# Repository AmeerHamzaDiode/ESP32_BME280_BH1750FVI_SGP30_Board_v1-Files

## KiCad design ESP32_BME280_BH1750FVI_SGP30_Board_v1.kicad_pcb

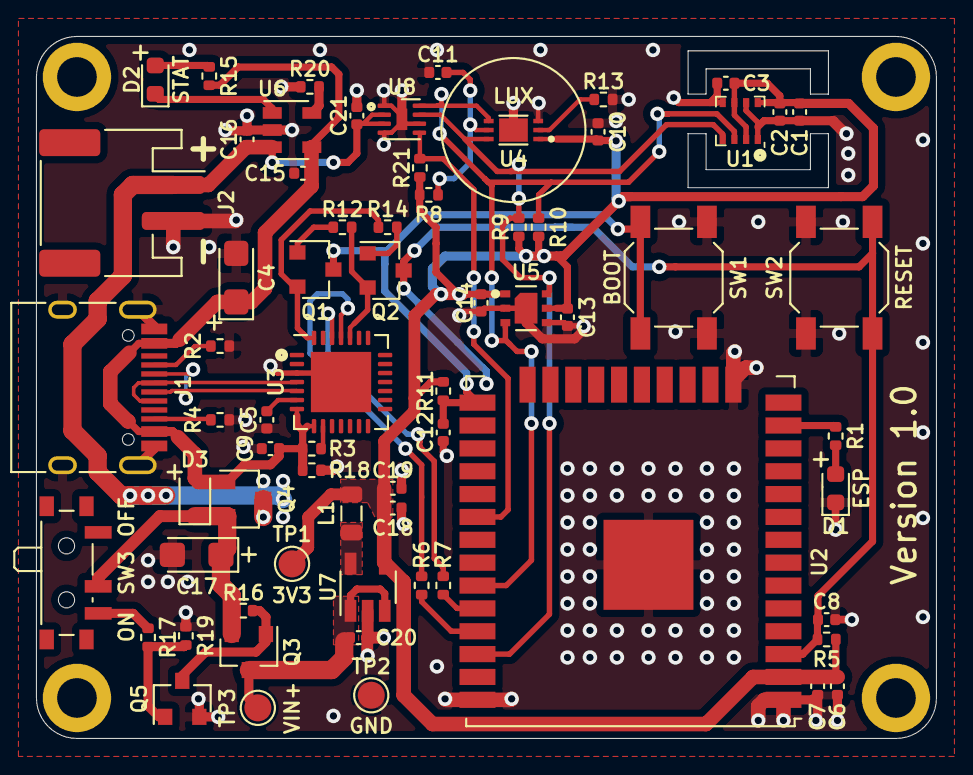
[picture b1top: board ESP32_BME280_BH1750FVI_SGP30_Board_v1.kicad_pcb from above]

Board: 2 copper layers, 50.0 x 39.0 mm, 71 parts (0 on the bottom side), 36 nets.

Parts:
C1, C6, C15, C16, C18: 10uF; C_0402_1005Metric
C2, C3, C5, C7, C9, C10, C14, C19, C21: 0.1uF; C_0402_1005Metric
C4, C17: 10uF; CP_EIA-3216-18_Kemet-A
C8, C11, C12, C13: 1uF; C_0402_1005Metric
C20: 4.7uF; C_0402_1005Metric
D1: ESP; LED_0603_1608Metric
D2: STAT; LED_0603_1608Metric
D3: 1N5819WS; D_SOD-323
H1, H2, H3, H4: M2; MountingHole_2.2mm_M2_DIN965_Pad
J1: TYPE-C-31-M-12; USB_C_Receptacle_HRO_TYPE-C-31-M-12
J2: S2B-PH; JST_PH_S2B-PH-SM4-TB_1x02-1MP_P2.00mm_Horizontal
L1: 2.2uH; L_0805_2012Metric
Q1, Q2: SS8050; SOT-23
Q3, Q4: SI2301CDS-T1-GE3; SOT-23
Q5: 2N7002; SOT-23
R1, R17: 470R; R_0402_1005Metric
R2, R4: 5.1K; R_0402_1005Metric
R3, R5, R9, R10, R11, R12, R14, R16, R19, R21: 10K; R_0402_1005Metric
R6, R7, R8, R13, R15: 1K; R_0402_1005Metric
R18: 100K; R_0402_1005Metric
R20: 2K; R_0402_1005Metric
SW1: BOOT; SW_SPST_SKQG_WithoutStem
SW2: RESET; SW_SPST_SKQG_WithoutStem
SW3: K3-1296S-E1; Slide_switch_K3-1296S-E1
TP1: 3V3; TestPoint_Pad_D1.5mm
TP2: GND; TestPoint_Pad_D1.5mm
TP3: VIN+; TestPoint_Pad_D1.5mm
U1: BME280; Bosch_LGA-8_2.5x2.5mm_P0.65mm_ClockwisePinNumbering
U2: ESP32-WROOM-32UE-N8; ESP32-WROOM-32U
U3: CP2102-GMR; QFN-28-1EP_5x5mm_P0.5mm_EP3.35x3.35mm
U4: BH1750FVI-TR
U5: SGP30-2.5K; SGP40-D-R4
U6: MCP73831T-2ACI/OT; SOT-23-5
U7: LM3671MFX-3.3/NOPB; TSOT-23-5
U8: MAX17048G+T10; DFN-8-1EP_2x2mm_P0.5mm_EP0.6x1.2mm

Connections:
+3V3: C1.1, C2.1, C3.1, C6.1, C7.1, C10.1, C13.1, C14.1, C18.1, C19.1, L1.2, R5.2, R8.1, R9.1, R10.1, R11.2, R21.1, TP1.1, U1.2, U1.6, U1.8, U2.2, U4.1, U5.1, U5.5, U7.4
+BATT: C16.1, C21.1, J2.1, Q4.3, U6.3, U8.2, U8.3
/PWR+: C17.1, D3.1, Q3.2, Q4.2, R16.1, SW3.2
/VIN+: C20.1, Q3.3, TP3.1, U7.1, U7.3
BOOT: C12.1, Q1.3, R11.1, SW1.2, U2.25
D+: J1.A6, J1.B6, U3.4
D-: J1.A7, J1.B7, U3.5
DTR: Q1.2, R14.1, U3.28
GND: C1.2, C2.2, C3.2, C4.2, C5.2, C6.2, C7.2, C8.2, C9.2, C10.2, C11.2, C12.2, C13.2, C14.2, C15.2, C16.2, C17.2, C18.2, C19.2, C20.2, C21.2, D1.1, J1.A1, J1.A12, J1.B1, J1.B12, J1.S1, J2.2, Q5.2, R2.1, R4.1, R13.2, R18.2, R19.2, R20.2, SW1.1, SW2.1, TP2.1, U1.1, U1.5, U1.7, U2.1, U2.15, U2.38, U2.39, U3.3, U3.29, U4.3, U4.7, U5.2, U5.4, U5.7, U6.2, U7.2, U8.1, U8.4, U8.6, U8.9
IO14: R1.1, U2.13
IO18: R21.2, U2.30, U8.5
unnamed: C5.1, U3.6
unnamed: C11.1, R8.2, U4.5
unnamed: D1.2, R1.2
unnamed: D2.1, U6.1
unnamed: D2.2, R15.2
unnamed: J1.A5, R2.2
unnamed: J1.B5, R4.2
unnamed: L1.1, U7.5
unnamed: Q1.1, R12.2
unnamed: Q2.1, R14.2
unnamed: Q3.1, Q5.3, R16.2
unnamed: Q5.1, R17.1, R19.1
unnamed: R3.2, U3.9
unnamed: R6.1, U2.35
unnamed: R7.2, U2.34
unnamed: R13.1, U4.2
unnamed: R17.2, SW3.3
unnamed: R20.1, U6.5
RESET: C8.1, Q2.3, R5.1, SW2.2, U2.3
RTS: Q2.2, R12.1, U3.24
RXD: R6.2, U3.25
SCL: R9.2, U1.4, U2.36, U4.6, U5.6, U8.7
SDA: R10.2, U1.3, U2.33, U4.4, U5.3, U8.8
TXD: R7.1, U3.26
VBUS: C4.1, C9.1, C15.1, D3.2, J1.A4, J1.A9, J1.B4, J1.B9, Q4.1, R3.1, R15.1, R18.1, U3.7, U3.8, U6.4

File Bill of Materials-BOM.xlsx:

Designator | Comment | Quantity | Footprint | Manufacturer Name | Manufacturer Part # | JLCPCB Part #
C18,C16,C15,C6,C1 | 10uF | 5 | C_0402_1005Metric | Samsung Electro-Mechanics | CL05A106MQ5NUNC | C15525
C21,C19,C14,C10,C9,C7,C5,C3,C2 | 0.1uF | 9 | C_0402_1005Metric | Samsung Electro-Mechanics | CL05B104KO5NNNC | C1525
C17,C4 | 10uF | 2 | CP_EIA-3216-18_Kemet-A | KYOCERA AVX | TAJA106K016RNJ | C7171
C13,C12,C11,C8 | 1uF | 4 | C_0402_1005Metric | Samsung Electro-Mechanics | CL05A105KA5NQNC | C52923
C20 | 4.7uF | 1 | C_0402_1005Metric | Samsung Electro-Mechanics | CL05A475MP5NRNC | C23733
D1 | ESP | 1 | LED_0603_1608Metric | Hubei KENTO Elec | KT-0603W | C2290
D2 | STAT | 1 | LED_0603_1608Metric | Hubei KENTO Elec | KT-0603R | C2286
D3 | 1N5819WS | 1 | D_SOD-323 | Guangdong Hottech | 1N5819WS | C191023
J1 | TYPE-C-31-M-12 | 1 | USB_C_Receptacle_HRO_TYPE-C-31-M-12 | Korean Hroparts Elec | TYPE-C-31-M-12 | C165948
J2 | S2B-PH | 1 | JST_PH_S2B-PH-SM4-TB_1x02-1MP_P2.00mm_Horizontal | JST | S2B-PH-SM4-TB(LF)(SN) | C295747
L1 | 2.2uH | 1 | L_0805_2012Metric | FH (Guangdong Fenghua Advanced Tech) | CMH201209B2R2MTD | C394957
Q2,Q1 | SS8050 | 2 | SOT-23 | Jiangsu Changjing Electronics Technology Co., Ltd. | SS8050(RANGE:200-350) | C2150
Q4,Q3 | SI2301CDS-T1-GE3 | 2 | SOT-23 | Vishay Intertech | SI2301CDS-T1-GE3 | C10487
Q5 | 2N7002 | 1 | SOT-23 | Jiangsu Changjing Electronics Technology Co., Ltd. | 2N7002 | C8545
R17,R1 | 470R | 2 | R_0402_1005Metric | UNI-ROYAL(Uniroyal Elec) | 0402WGF4700TCE | C25117
R4,R2 | 5.1K | 2 | R_0402_1005Metric | UNI-ROYAL(Uniroyal Elec) | 0402WGF5101TCE | C25905
R21,R19,R16,R14,R12,R11,R10,R9,R5,R3 | 10K | 10 | R_0402_1005Metric | UNI-ROYAL(Uniroyal Elec) | 0402WGF1002TCE | C25744
R15,R13,R8,R7,R6 | 1K | 5 | R_0402_1005Metric | UNI-ROYAL(Uniroyal Elec) | 0402WGF1001TCE | C11702
R18 | 100K | 1 | R_0402_1005Metric | UNI-ROYAL(Uniroyal Elec) | 0402WGF1003TCE | C25741
R20 | 2K | 1 | R_0402_1005Metric | UNI-ROYAL(Uniroyal Elec) | 0402WGF2001TCE | C4109
SW1 | BOOT | 1 | SW_SPST_SKQG_WithoutStem | XKB Connection | TS-1187A-B-A-B | C318884
SW2 | RESET | 1 | SW_SPST_SKQG_WithoutStem | XKB Connection | TS-1187A-B-A-B | C318884
SW3 | K3-1296S-E1 | 1 | Slide_switch_K3-1296S-E1 | Korean Hroparts Elec | K3-1296S-E1 | C128955
U1 | BME280 | 1 | Bosch_LGA-8_2.5x2.5mm_P0.65mm_ClockwisePinNumbering | Bosch Sensortec | BME280 | C92489
U2 | ESP32-WROOM-32UE-N8 | 1 | ESP32-WROOM-32U | Espressif Systems | ESP32-WROOM-32UE-N8 | C701345
U3 | CP2102-GMR | 1 | QFN-28-1EP_5x5mm_P0.5mm_EP3.35x3.35mm | SKYWORKS/SILICON LABS | CP2102-GMR | C6568
U4 | BH1750FVI-TR | 1 | BH1750FVI-TR | ROHM Semicon | BH1750FVI-TR | C78960
U5 | SGP30-2.5K | 1 | SGP40-D-R4 | Sensirion | SGP30-2.5k | C514454
U6 | MCP73831T-2ACI/OT | 1 | SOT-23-5 | Microchip Tech | MCP73831T-2ACI/OT | C424093
U7 | LM3671MFX-3.3/NOPB | 1 | TSOT-23-5 | Texas Instruments | LM3671MFX-3.3/NOPB | C477918
U8 | MAX17048G+T10 | 1 | DFN-8-1EP_2x2mm_P0.5mm_EP0.6x1.2mm | Analog Devices Inc./Maxim Integrated | MAX17048G+T10 | C2682616
